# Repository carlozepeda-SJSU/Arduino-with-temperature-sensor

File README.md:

# Arduino Environmental Monitor

## Overview

This is a project I worked on to learn how to use the Arduino R4 board while also building a practical device that monitors the temperature, power drawn, time and displays it on a small screen. Throughout the time I worked on this project I gained experience with the Arduino IDE, common electronic used libraries, electronic components, circuit design, and integrated multiple modules into a single working system.
What began as a simple breadboard prototype eventually evolved into a complete hardware project. After making sure that the circuit I designed worked, I wanted to make it more professional looking. I created a custom PCB that mounts directly on top of the Arduino Uno R4, creating a much cleaner and more reliable design with fewer jumper wires.

The finished project displays environmental data, power consumption, and the current time on a 1.3-inch OLED display.

---

## Features

- Measures ambient temperature, humidity, and air pressure using a BME280 sensor
- Obtains voltage and current drawn using an INA219 sensor
- Displays information on a 1.3 inch OLED display
- Synchronizes a clock over WiFi for an accurate local time
- Push buttons were placed to navigate between different display screens
- Custom PCB shield HAT designed in KiCad for a clean final build

## Development of the Project

### Phase 1 - Breadboard Prototype

The project started with just a breadboard and temperature sensor displaying information on the Arduino IDE. For someone who had never built a project on their own, this was the hardest part. Understanding how libraries work and finding which library is needed for the electronic components was not easy at first. Coding was another part of the project that I was not confident about, however as I kept learning more and expanding the project, I gained more knowledge and confidence.
Once everything implemented was working as intended, I decided that it was time to take the next step.

Features included:
- BME280 environmental sensor
- INA219 current sensor
- OLED display
- Arduino Uno R4

### Phase 2 - Custom PCB

While the breadboard prototype was working as intended, I wanted to make it look less messy and more like a finished product. So I designed a custom PCB in KiCad that mounts directly on top of the Arduino Uno R4. This part helped me understand the KiCAD work flow. From deciding where to place the components, to finding the right footprints. This part was a lot of trial and error, but I am satisfied with the end product.

The PCB includes:
- Through hole components
- Push buttons for the user input
- Headers for the modules
- Integrated power distribution
- Cleaner wiring with a compact layout

## Hardware Used

- Arduino Uno R4 WiFi
- BME280 Environmental Sensor
- INA219 Current Sensor
- 1.3 inch 128×64  OLED Display
- Custom KiCad PCB
- Push Buttons
- DC Barrel Jack
- Breadboard with jumper wires (prototype phase)

## What I Learned

Throughout this project I learned how to:

- Program using the Arduino IDE
- Read sensor data over I²C
- Use commonly used Arduino libraries
- Debug hardware and software issues
- Design PCBs using KiCad
- Route traces and prepare a board for manufacturing
- Solder through hole components
- Integrate multiple modules into a single embedded system
- Synchronize time over Wi-Fi using the Arduino Uno R4

## Project Gallery

### Hardware Layout

The completed breadboard prototype showing all connected components.

[Prototype Images](Images_of_Prototype/)

The completed PCB HAT assembled 

[PCB Images](Images_of_PCB_HAT/)

## Future Improvements

- Design a second revision of the PCB
- Design a 3D printed enclosure
- Add data logging to an SD card
- Create a web dashboard for remote monitoring

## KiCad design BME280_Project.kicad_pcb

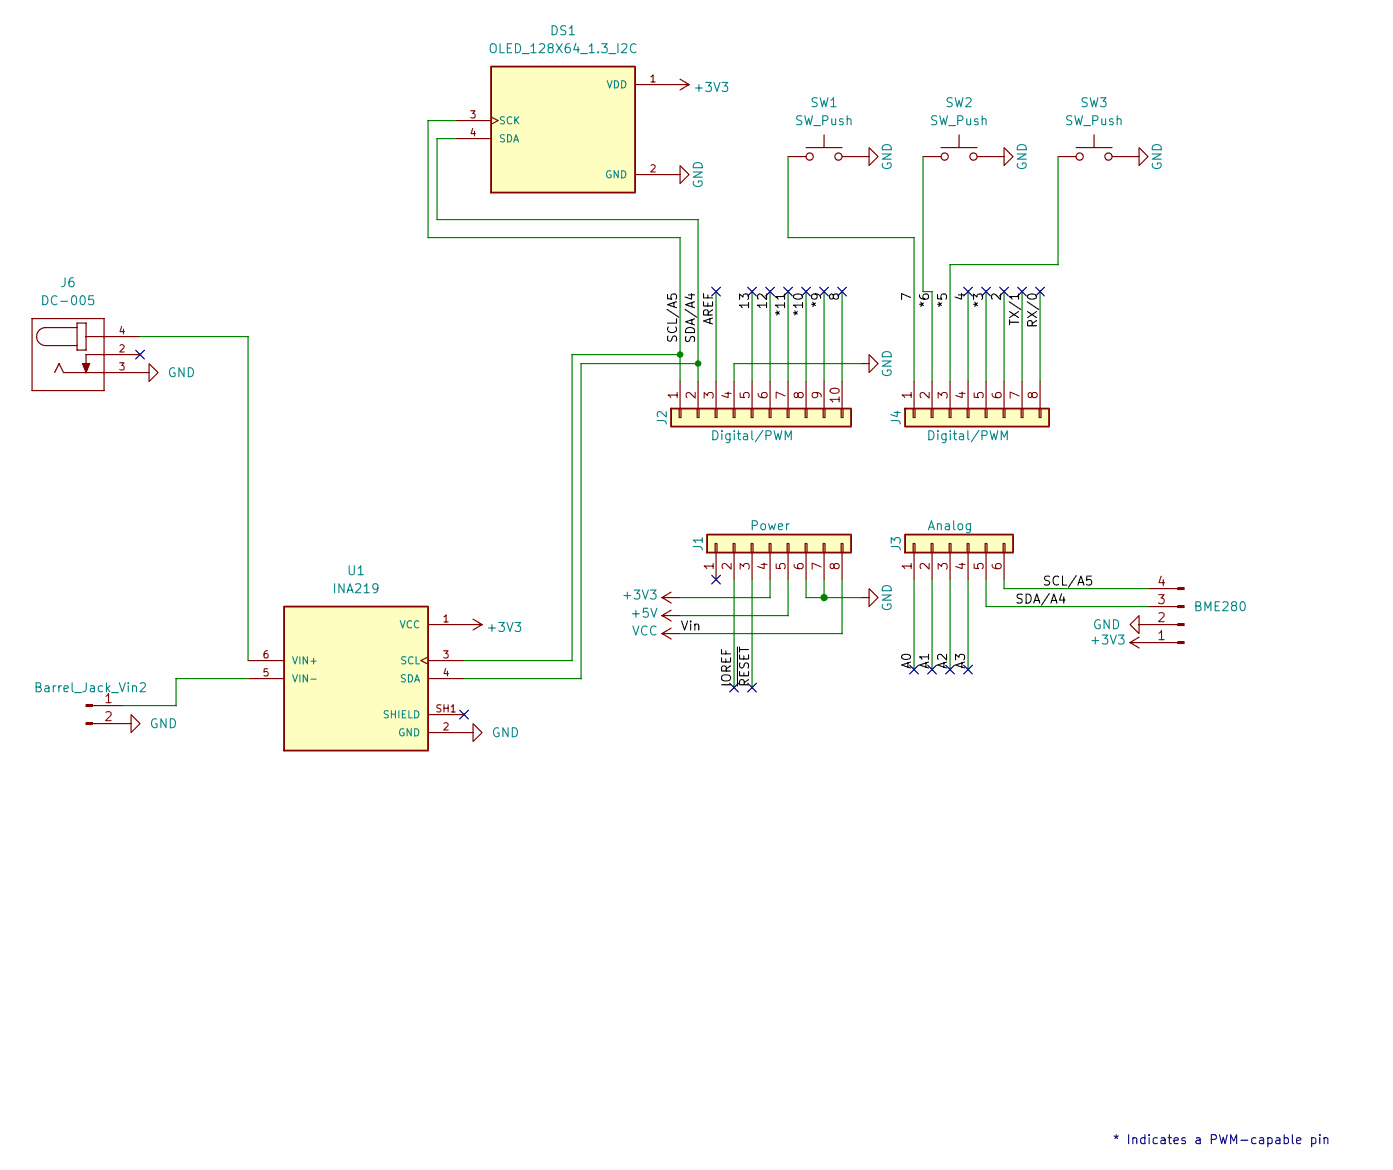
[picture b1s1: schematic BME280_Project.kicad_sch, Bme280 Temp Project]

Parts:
BME280: Conn_01x04_Pin; PinHeader_1x04_P2.54mm_Vertical
Barrel_Jack_Vin2: Conn_01x02_Pin; PinHeader_1x02_P2.54mm_Vertical
DS1: OLED_128X64_1.3_I2C; LCD_OLED_128X64_1.3_I2C; PARTREV NA
J1: Power; PinSocket_1x08_P2.54mm_Vertical
J2: Digital/PWM; PinSocket_1x10_P2.54mm_Vertical
J3: Analog; PinSocket_1x06_P2.54mm_Vertical
J4: Digital/PWM; PinSocket_1x08_P2.54mm_Vertical
J6: DC-005; NINIGI_DC-005
SW1, SW2, SW3: SW_Push; SW_PUSH_6mm_H4.3mm
U1: INA219; MODULE_INA219; PARTREV C

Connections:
+3V3: BME280.1, DS1.1 (VDD), J1.4, U1.1 (VCC)
+5V: J1.5
/2: J4.6
/4: J4.4
/7: J4.1, SW1.1
/8: J2.10
/12: J2.6
/13: J2.5
/*3: J4.5
/*5: J4.3, SW3.1
/*6: J4.2, SW2.1
/*9: J2.9
/*10: J2.8
/*11: J2.7
/A0: J3.1
/A1: J3.2
/A2: J3.3
/A3: J3.4
/AREF: J2.3
/IOREF: J1.2
/RX/0: J4.8
/SCL/A5: BME280.4, DS1.3 (SCK), J2.1, J3.6, U1.3 (SCL)
/SDA/A4: BME280.3, DS1.4 (SDA), J2.2, J3.5, U1.4 (SDA)
/TX/1: J4.7
/~RESET: J1.3
GND: BME280.2, Barrel_Jack_Vin2.2, DS1.2 (GND), J1.6, J1.7, J2.4, J6.3, SW1.2, SW2.2, SW3.2, U1.2 (GND)
unnamed: Barrel_Jack_Vin2.1, U1.5 (VIN-), U1.VIN-
unnamed: J6.4, U1.6 (VIN+), U1.VIN+
VCC: J1.8

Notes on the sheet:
* Indicates a PWM-capable pin

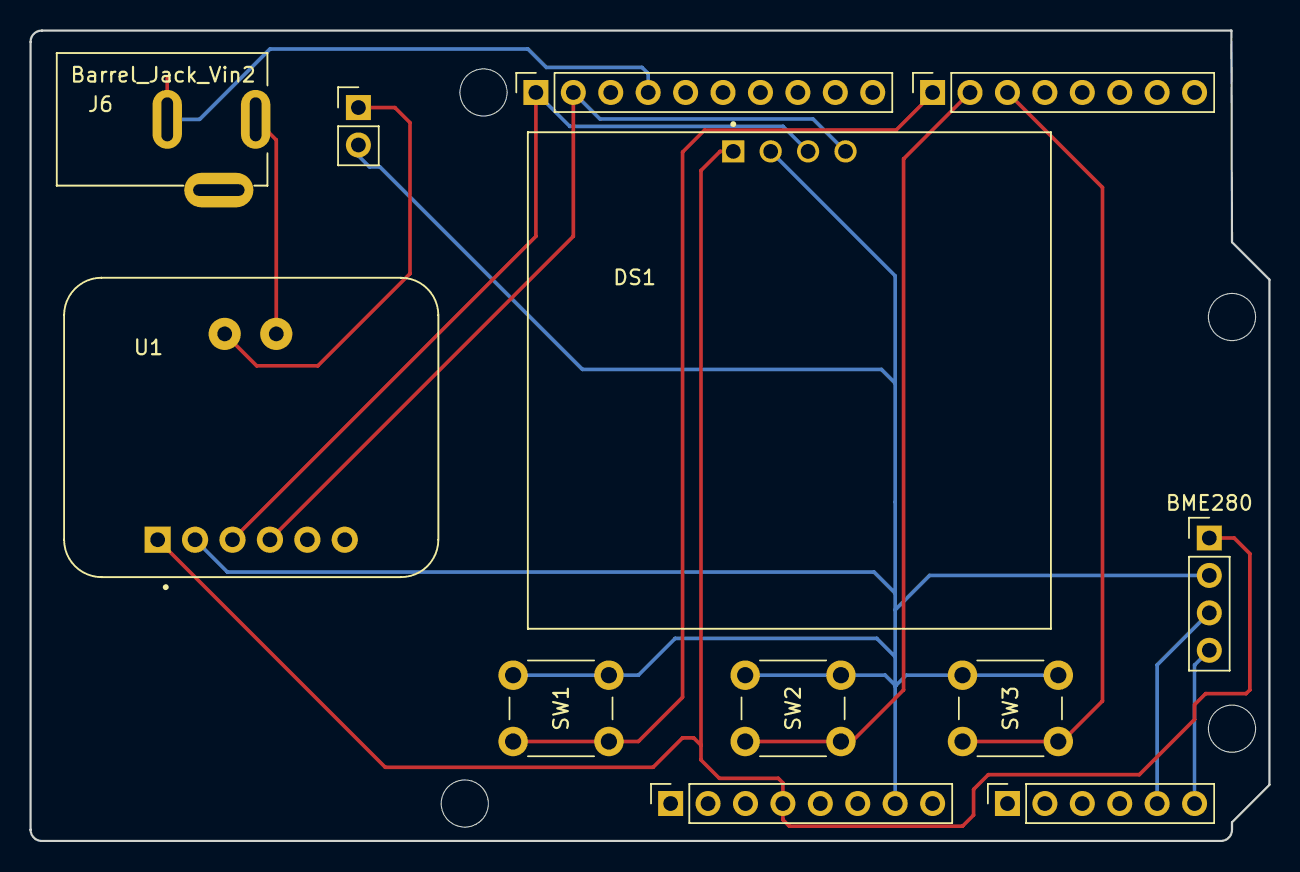
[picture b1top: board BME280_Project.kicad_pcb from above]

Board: 2 copper layers, 84.1 x 55.0 mm, 16 parts (0 on the bottom side), 9 nets.

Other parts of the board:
MH1, MH2, MH3, MH4: MountingHole_3.2mm
